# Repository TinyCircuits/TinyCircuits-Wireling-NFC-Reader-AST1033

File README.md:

# TinyCircuits Wireling NFC Reader
# AST1033 Rev1

The design files are located under design_files/ for the TinyCircuits AST1033 Rev 1 PCB. This is a Wireling board which features the MFRC522 RFID Reader and is designed to communicate with ISO/IEC 14443 A/MIFARE cards and transponders.

Format is in Cadsoft Eagle format - Eagle version 6.2 was used for the original design.

For more infomation on this, check out the product page at TinyCircuits.com

# License:

Design by TinyCircuits.
All design files are released under the Creative Commons Attribution Share-Alike 3.0 License, see the following link for details: http://creativecommons.org/licenses/by-sa/3.0

All text above must be included in any redistribution or derived design

This project uses designs and concepts developed as part of the Arduino project and the LilyPad project.  The TinyCircuits design files themselves (schematics, PCB and libraries) are not directly derived from these works' design files and have been created new, however the concepts and basic architecture behind the TinyDuino and TinyLily products are derived and we thank the hard work of the organizations below for their contributions to open-source hardware:
  
Original Arduino Uno Design by Team Arduino

LilyPad Arduino Design by Leah Buechley and Sparkfun Electronics

Please support the open-source hardware community

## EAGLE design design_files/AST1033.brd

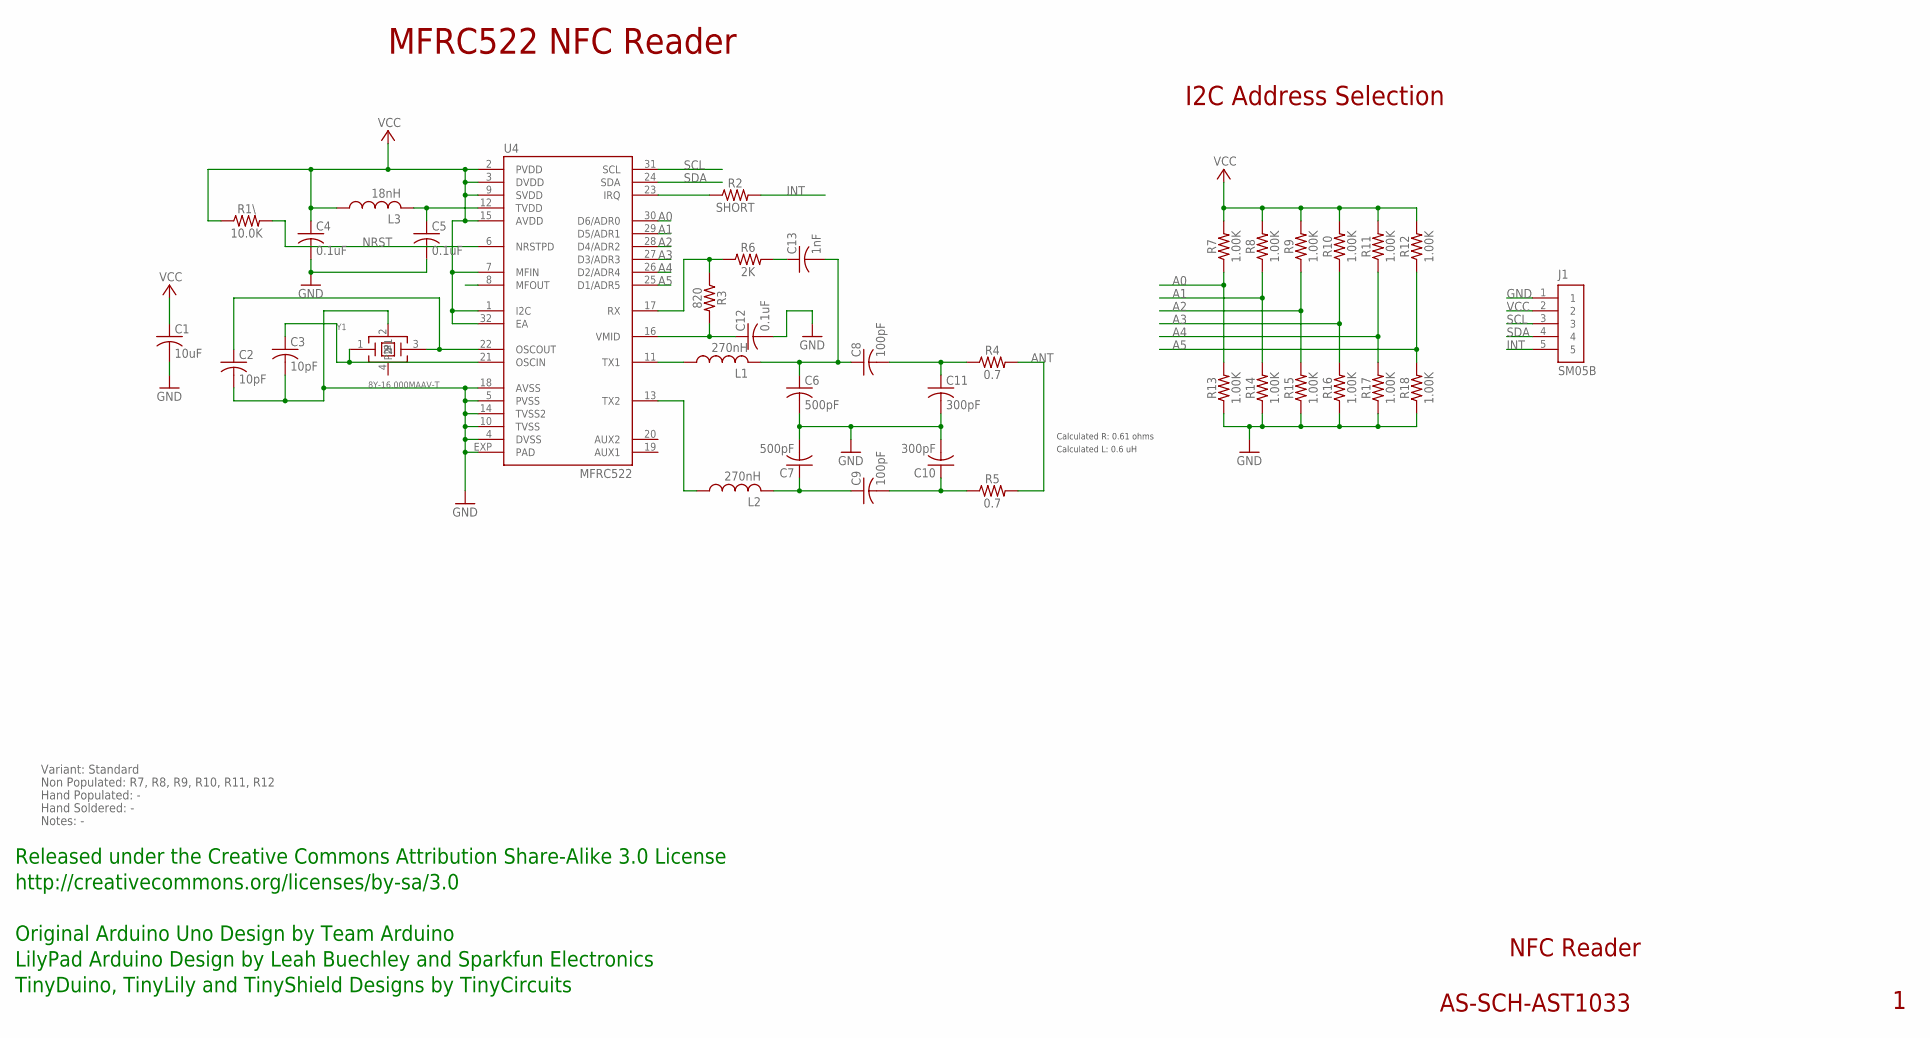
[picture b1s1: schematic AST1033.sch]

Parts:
C1: 10uF; C0603; PARTNO AS-ITM-00002
C2, C3: 10pF; C0402
C4, C5, C12: 0.1uF; C0402; PARTNO AS-ITM-00008
C6, C7: 500pF; 0402; PARTNO AS-ITM-00148
C8, C9: 100pF; 0402; PARTNO AS-ITM-00148
C10, C11: 300pF; C0402; PARTNO AS-ITM-00008
C13: 1nF; C0402; PARTNO AS-ITM-00008
J1: SM05B; JST_SH_5X1
L1, L2: 270nH; C0402; PARTNO AS-ITM-00250
L3: 18nH; C0402
R1\: 10.0K; 0402
R2: SHORT; 0402_SHORT
R3: 820; 0402; PARTNO AS-ITM-00076
R4, R5: 0.7; 0402
R6: 2K; 0402; PARTNO AS-ITM-00315
R7, R8, R9, R10, R11, R12, R13, R14, R15, R16, R17, R18: 1.00K; 0402
U4: MFRC522; ATMEL_QFN32
Y1: 8Y-16.000MAAV-T; ABM11

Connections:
A0: R7.1, R13.2, U4.30 (D6/ADR0)
A1: R8.1, R14.2, U4.29 (D5/ADR1)
A2: R9.1, R15.2, U4.28 (D4/ADR2)
A3: R10.1, R16.2, U4.27 (D3/ADR3)
A4: R11.1, R17.2, U4.26 (D2/ADR4)
A5: R12.1, R18.2, U4.25 (D1/ADR5)
ANT: R4.2, R5.2
GND: C1.2, C2.2, C3.2, C4.2, C5.2, C6.2, C7.2, C10.2, C11.2, C12.2, J1.1, R13.1, R14.1, R15.1, R16.1, R17.1, R18.1, U4.4 (DVSS), U4.5 (PVSS), U4.10 (TVSS), U4.14 (TVSS2), U4.18 (AVSS), U4.EXP (PAD), Y1.2
INT: J1.5, R2.2
unnamed: R2.1, U4.23 (IRQ)
unnamed: L1.1, U4.11 (TX1)
unnamed: L2.1, U4.13 (TX2)
unnamed: C6.1, C8.1, C13.2, L1.2
unnamed: R3.1, R6.1, U4.17 (RX)
unnamed: C7.1, C9.1, L2.2
unnamed: C2.1, U4.22 (OSCOUT), Y1.3 (2)
unnamed: C3.1, U4.21 (OSCIN), Y1.1
unnamed: C9.2, C10.1, R5.1
unnamed: C12.1, R3.2, U4.16 (VMID)
unnamed: C8.2, C11.1, R4.1
unnamed: C5.1, L3.2, U4.12 (TVDD)
unnamed: C13.1, R6.2
NRST: R1\.2, U4.6 (NRSTPD)
SCL: J1.3, U4.31 (SCL)
SDA: J1.4, U4.24 (SDA)
VCC: C1.1, C4.1, J1.2, L3.1, R1\.1, R7.2, R8.2, R9.2, R10.2, R11.2, R12.2, U4.1 (I2C), U4.2 (PVDD), U4.3 (DVDD), U4.7 (MFIN), U4.9 (SVDD), U4.15 (AVDD), U4.32 (EA)

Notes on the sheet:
NFC Reader
AS-SCH-AST1033
Released under the Creative Commons Attribution Share-Alike 3.0 License
http://creativecommons.org/licenses/by-sa/3.0
LilyPad Arduino Design by Leah Buechley and Sparkfun Electronics
TinyDuino, TinyLily and TinyShield Designs by TinyCircuits
Original Arduino Uno Design by Team Arduino
Calculated L: 0.6 uH
Calculated R: 0.61 ohms
I2C Address Selection
MFRC522 NFC Reader
Non Populated: R7, R8, R9, R10, R11, R12
Hand Populated: -
Hand Soldered: -
Variant: Standard
Notes: -

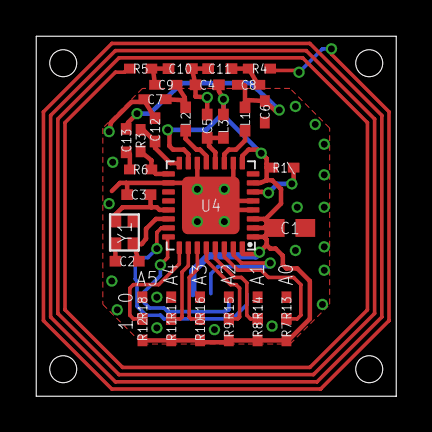
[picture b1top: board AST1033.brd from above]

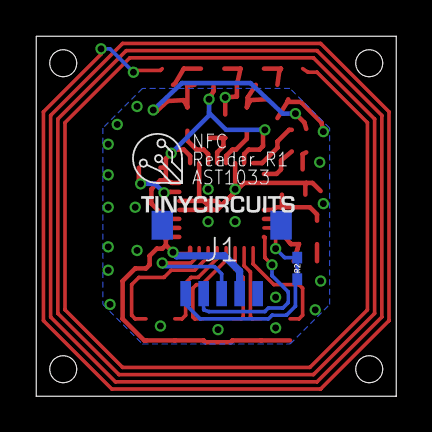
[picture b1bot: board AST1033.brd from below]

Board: 2 copper layers, 20.0 x 20.0 mm, 38 parts (2 on the bottom side), 26 nets.

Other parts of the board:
U$1: DOCFIELD-TINYCIRCUITS-PCB

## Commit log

2019-10-01 datasheet
2019-12-17 updated documentation
